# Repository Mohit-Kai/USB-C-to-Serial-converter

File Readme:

# SURE-TRUST-PROJECTS-G4-PCB

This USB-C to Serial converter board is built around the reliable CH340C interface IC, designed for programming and debugging microcontrollers. It provides standard serial signals (TX, RX, DTR) with selectable logic levels of 3.3V or 5V. Integrated TX/RX status LEDs offer visual indication of data transmission and reception. Compact and versatile, the board is well-suited for development and diagnostic applications

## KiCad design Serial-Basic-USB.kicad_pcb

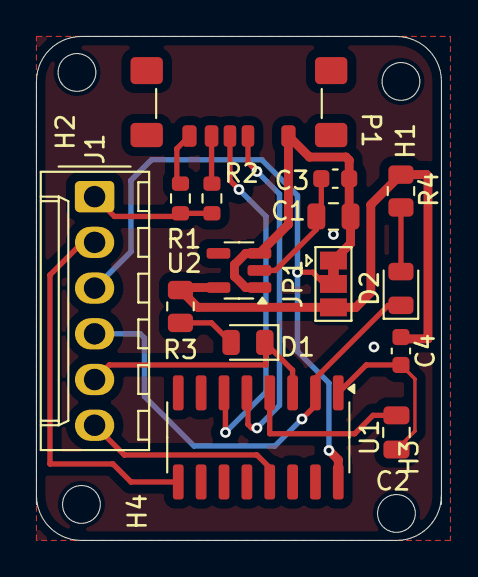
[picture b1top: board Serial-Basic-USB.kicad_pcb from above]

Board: 2 copper layers, 22.5 x 28.0 mm, 19 parts (0 on the bottom side), 15 nets.

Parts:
C1: 0.1uF; C_0805_2012Metric
C2: 10nF; C_0805_2012Metric
C3, C4: 1uF; C_0603_1608Metric
D1, D2: LED; LED_0805_2012Metric
H1, H2, H3, H4: MountingHole; MountingHole_2.1mm
J1: Conn_01x06_Pin; Molex_KK-254_AE-6410-06A_1x06_P2.54mm_Vertical
JP1: SolderJumper_3_Bridged12; SolderJumper-3_P1.3mm_Bridged12_Pad1.0x1.5mm
P1: USB_C_Plug_USB2.0; USB_C_Receptacle_GCT_USB4135-GF-A_6P_TopMnt_Horizontal
R1, R2: 5.1K; R_0603_1608Metric
R3, R4: 1K; R_0805_2012Metric
U1: CH340C; SOIC-16_3.9x9.9mm_P1.27mm
U2: AP2112K-3.3; SOT-23-5

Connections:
3.3V: C4.1, JP1.3 (B), R3.1, R4.1, U2.5 (VOUT)
5V: C1.1, C3.1, JP1.1 (A), P1.A4 (VBUS), U2.1 (VIN), U2.3 (EN)
GND: C1.2, C2.2, C3.2, C4.2, J1.1, R1.2, R2.2, U1.1 (GND), U2.2 (GND)
unnamed: D1.2 (A), R3.2
unnamed: D2.2 (A), R4.2
unnamed: P1.A5 (CC1), R2.1
unnamed: P1.B5 (CC2), R1.1
unnamed: P1.A6 (D+), U1.5 (UD+)
unnamed: P1.A7 (D-), U1.6 (UD-)
unnamed: C2.1, U1.4 (V3)
RXI: D1.1 (K), J1.5, U1.3 (RXD)
TXO: D2.1 (K), J1.4, U1.2 (TXD)
VCC: J1.3, JP1.2 (C), U1.16 (VCC)
~CTS: J1.2, U1.9 (~CTS)
~DTR: J1.6, U1.13 (~DTR)

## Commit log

2025-09-19 Create Readme
    This USB-C to Serial converter board is built around the reliable CH340C interface IC, designed for programming and debugging microcontrollers. It provides standard serial signals (TX, RX, DTR) with 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
2025-09-19 USB Serial
2025-09-19 Update Readme
    # SURE-TRUST-PROJECTS-G4-PCB
